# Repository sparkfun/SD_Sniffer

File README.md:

SD Sniffer
==========

[
*SD Sniffer (TOL-11468)*](https://www.sparkfun.com/products/11468)

The SD Sniffer allows you to hook up an external device to view SPI signals between an SD socket and SD card.

Repository Contents
-------------------
* **/Hardware** - All Eagle design files (.brd, .sch, .STL)
* **/Production** - Test bed files and production panel files

License Information
-------------------
The hardware is released under [Creative Commons ShareAlike 4.0 International](https://creativecommons.org/licenses/by-sa/4.0/).

Distributed as-is; no warranty is given.

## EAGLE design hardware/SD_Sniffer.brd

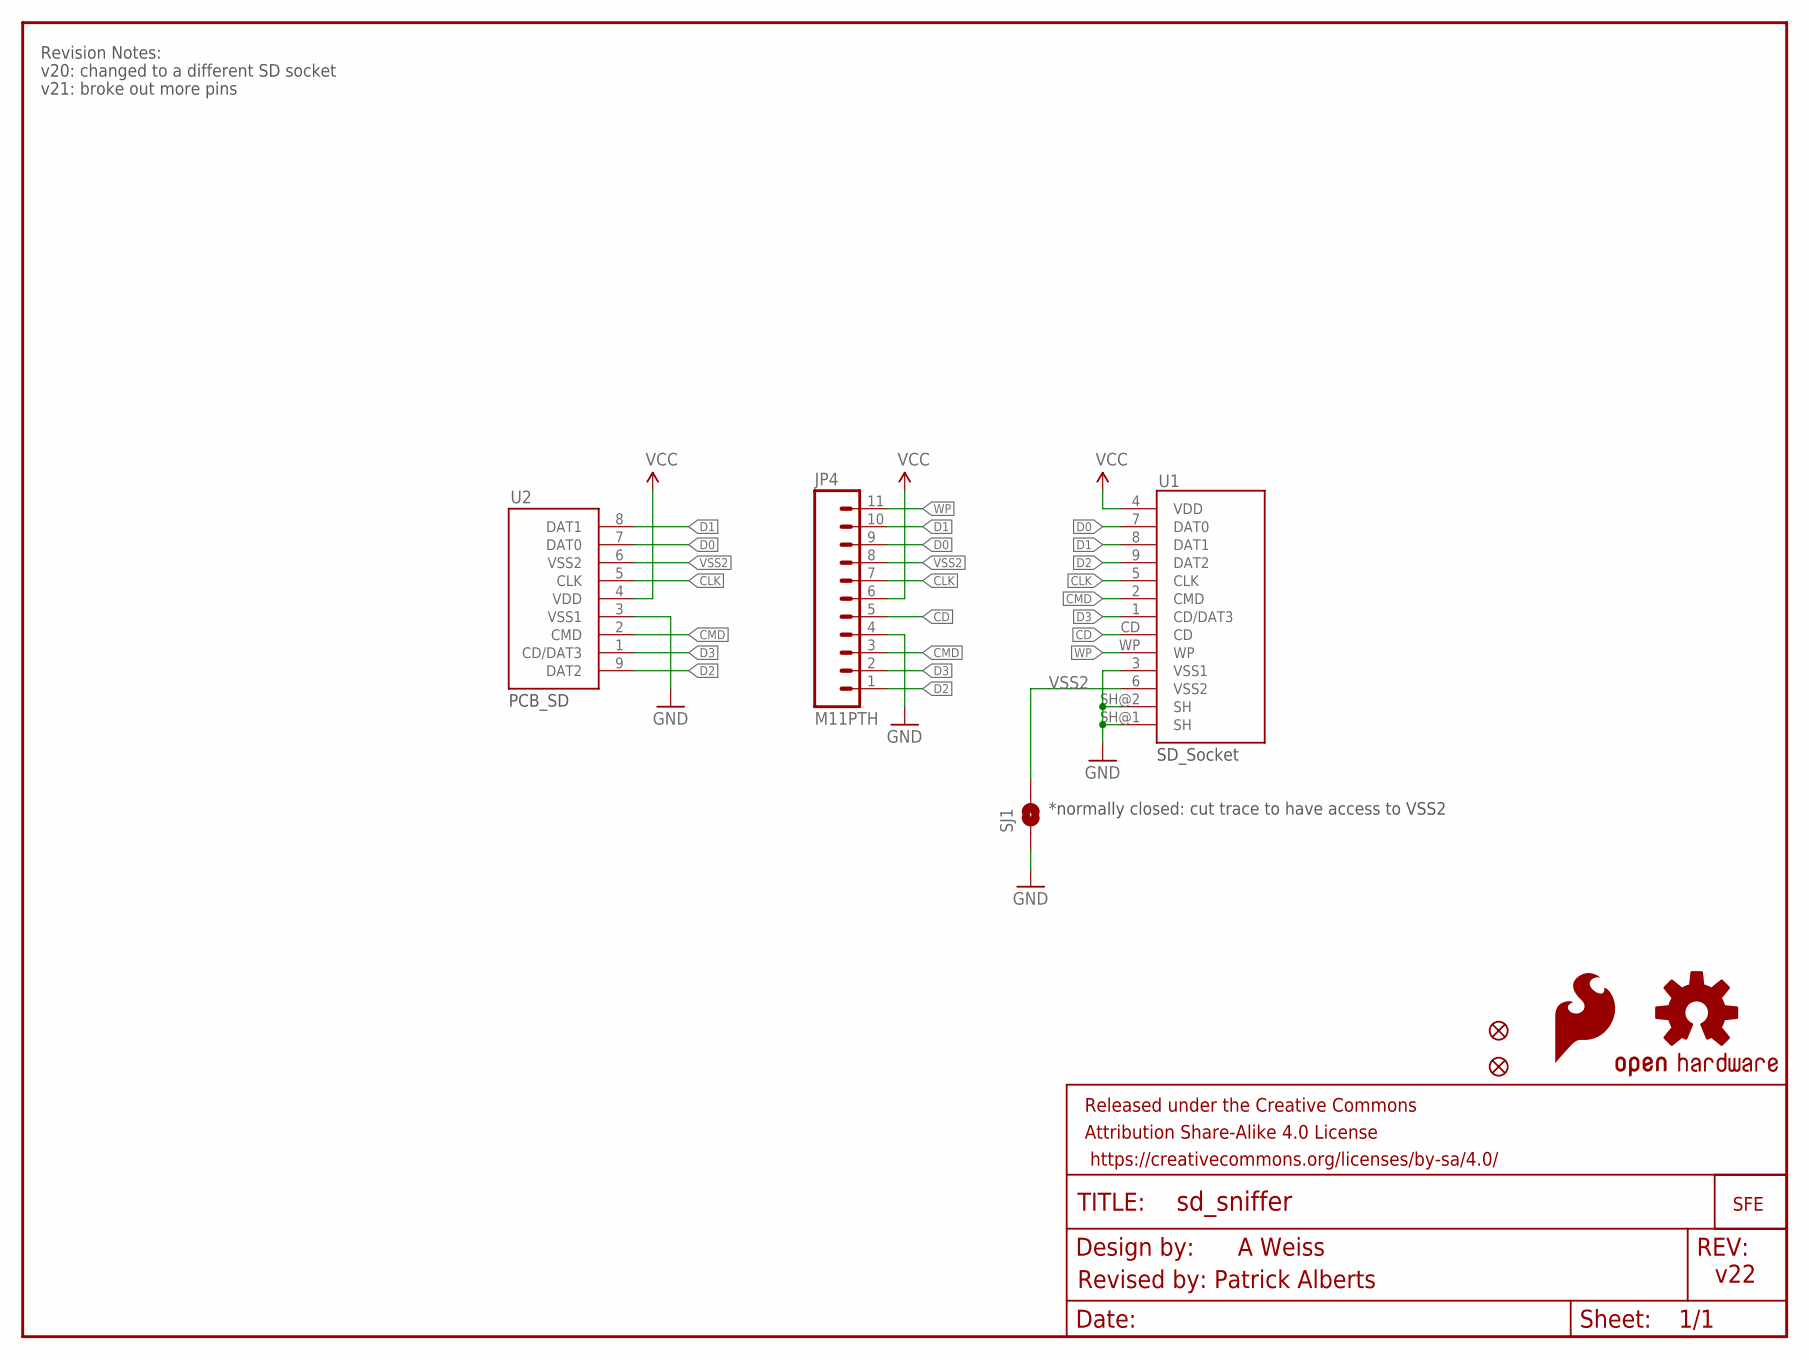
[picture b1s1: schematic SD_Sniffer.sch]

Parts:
FRAME1: FRAME-LETTER; CREATIVE_COMMONS
JP2, JP3: FIDUCIALUFIDUCIAL; MICRO-FIDUCIAL
JP4: M11PTH; 1X11
LOGO: LOGO-SFENEW; SFE-NEW-WEBLOGO
SJ1: SOLDERJUMPERTRACE; SJ_2S-TRACE
U1: SD_CARD_SOCKET; SD_1:1
U2: SD_MMC_CARDSD_PCB; SD-MMC-CARD
U$2: OSHW-LOGOS; OSHW-LOGO-S
U$4: SFE_LOGO_FLAME.2_INCH; SFE_LOGO_FLAME_.2

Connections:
CD: JP4.5, U1.CD
CLK: JP4.7, U1.5 (CLK), U2.5 (CLK)
CMD: JP4.3, U1.2 (CMD), U2.2 (CMD)
D0: JP4.9, U1.7 (DAT0), U2.7 (DAT0)
D1: JP4.10, U1.8 (DAT1), U2.8 (DAT1)
D2: JP4.1, U1.9 (DAT2), U2.9 (DAT2)
D3: JP4.2, U1.1 (CD/DAT3), U2.1 (CD/DAT3)
GND: JP4.4, SJ1.1, U1.3 (VSS1), U1.SH@1 (SH), U1.SH@2 (SH), U2.3 (VSS1)
VCC: JP4.6, U1.4 (VDD), U2.4 (VDD)
VSS2: JP4.8, SJ1.2, U1.6 (VSS2), U2.6 (VSS2)
WP: JP4.11, U1.WP

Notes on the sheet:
PCB_SD
SD_Socket
Revision Notes:
v20: changed to a different SD socket
*normally closed: cut trace to have access to VSS2
v21: broke out more pins
v22
A Weiss
Revised by: Patrick Alberts

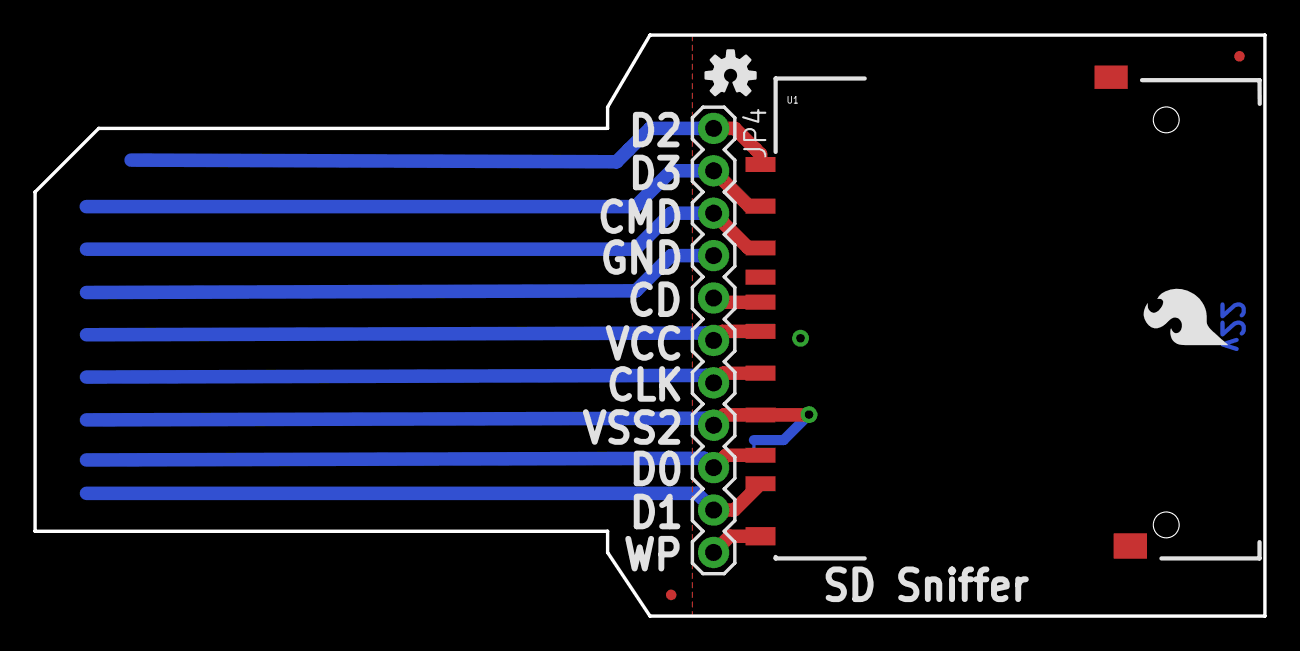
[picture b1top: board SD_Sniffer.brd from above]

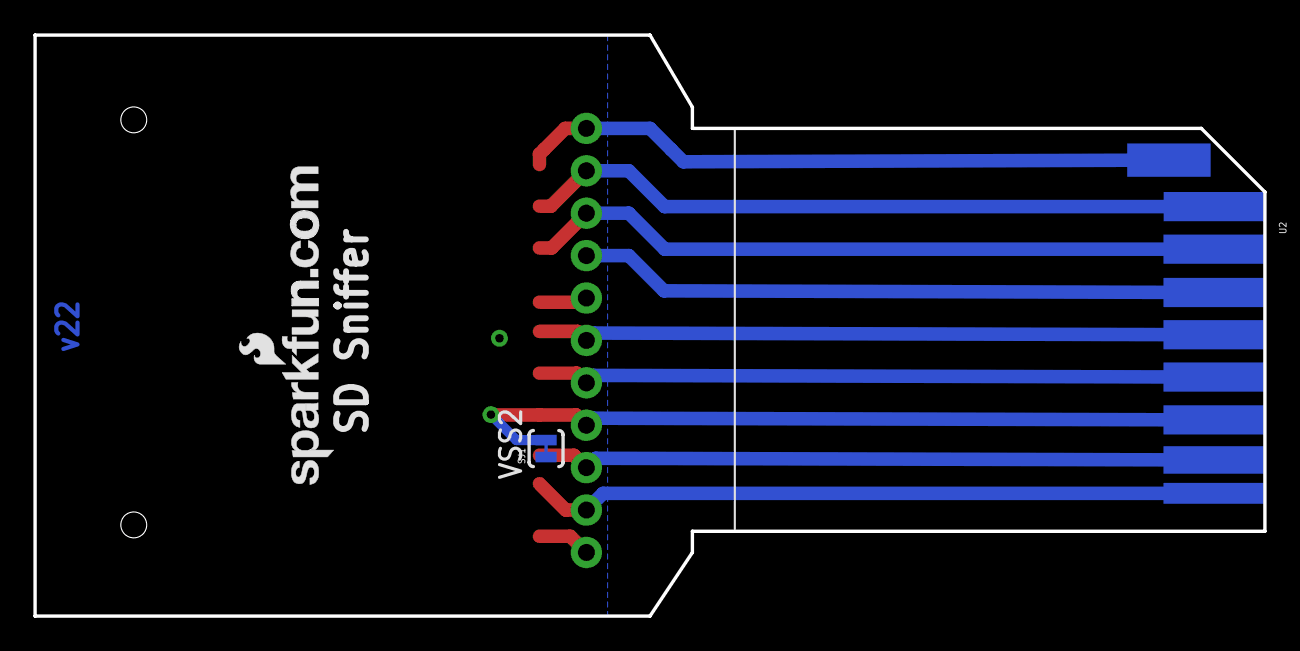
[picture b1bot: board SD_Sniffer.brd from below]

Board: 2 copper layers, 73.7 x 34.8 mm, 10 parts (3 on the bottom side), 11 nets.

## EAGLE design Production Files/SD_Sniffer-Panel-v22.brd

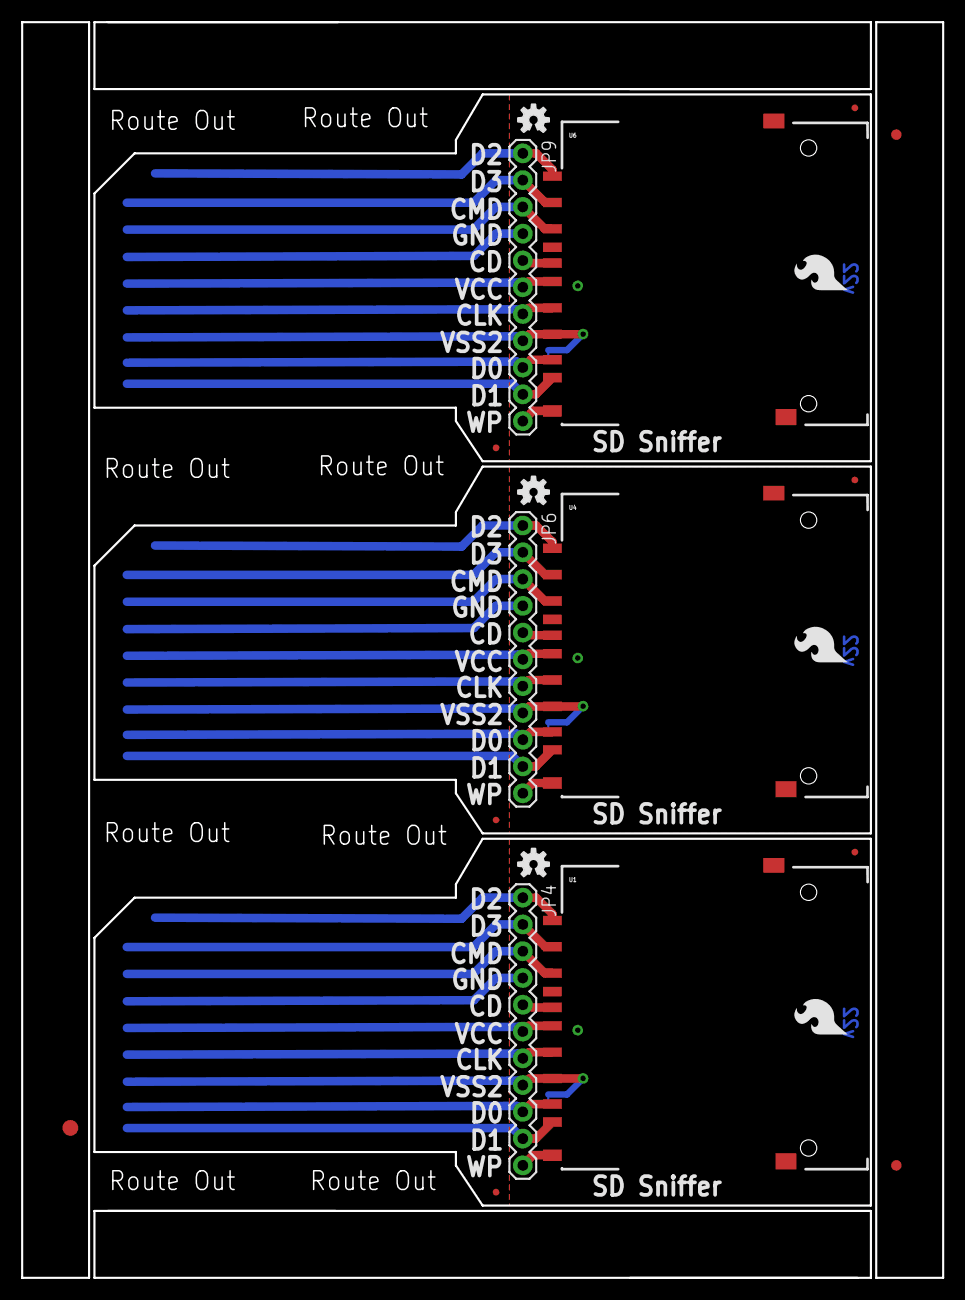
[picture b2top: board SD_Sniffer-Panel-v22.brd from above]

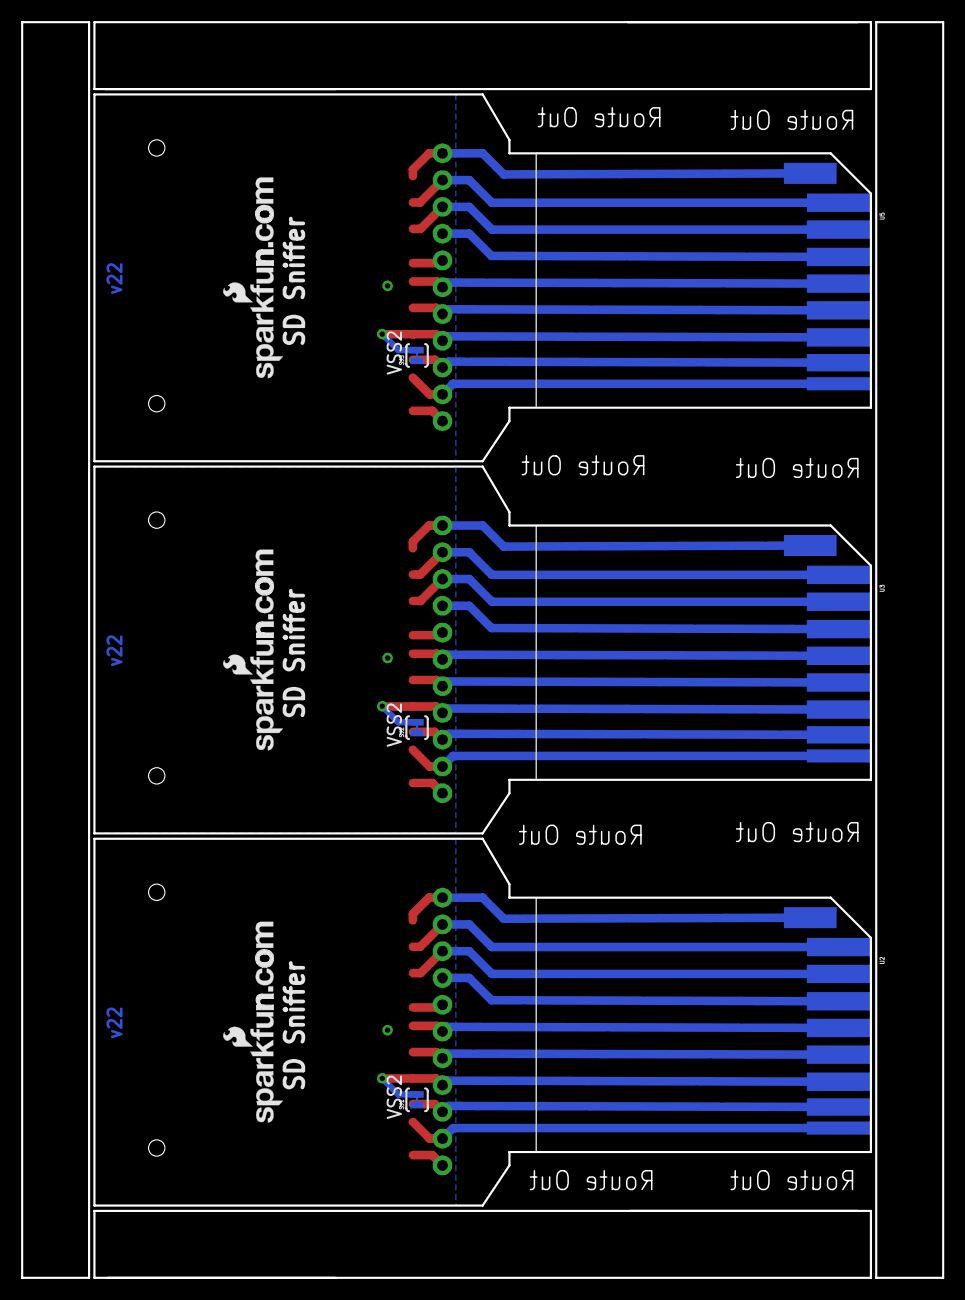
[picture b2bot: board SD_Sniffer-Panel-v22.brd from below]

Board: 2 copper layers, 87.4 x 119.1 mm, 30 parts (9 on the bottom side), 33 nets.

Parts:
E$1: FIDUCIAL-1.5X3
E$2, E$3: FIDUCIAL-1X2
JP1, JP2, JP3, JP5, JP7, JP8: FIDUCIALUFIDUCIAL; MICRO-FIDUCIAL
JP4, JP6, JP9: M11PTH; 1X11
LOGO, LOGO1, LOGO2: LOGO-SFENEW; SFE-NEW-WEBLOGO
SJ1, SJ2, SJ3: SOLDERJUMPERTRACE; SJ_2S-TRACE
U1, U4, U6: SD_CARD_SOCKET; SD_1:1
U2, U3, U5: SD_MMC_CARDSD_PCB; SD-MMC-CARD
U$1, U$4, U$5: SFE_LOGO_FLAME.2_INCH; SFE_LOGO_FLAME_.2
U$2, U$3, U$6: OSHW-LOGOS; OSHW-LOGO-S

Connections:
CD: JP4.5, U1.CD
CD1: JP6.5, U4.CD
CD2: JP9.5, U6.CD
CLK: JP4.7, U1.5, U2.5
CLK1: JP6.7, U3.5, U4.5
CLK2: JP9.7, U5.5, U6.5
CMD: JP4.3, U1.2, U2.2
CMD1: JP6.3, U3.2, U4.2
CMD2: JP9.3, U5.2, U6.2
D0: JP4.9, U1.7, U2.7
D1: JP4.10, U1.8, U2.8
D2: JP4.1, U1.9, U2.9
D3: JP4.2, U1.1, U2.1
D4: JP6.1, U3.9, U4.9
D5: JP6.9, U3.7, U4.7
D6: JP6.10, U3.8, U4.8
D7: JP6.2, U3.1, U4.1
D8: JP9.1, U5.9, U6.9
D9: JP9.9, U5.7, U6.7
D10: JP9.10, U5.8, U6.8
D11: JP9.2, U5.1, U6.1
GND: JP4.4, SJ1.1, U1.3, U1.SH@1, U1.SH@2, U2.3
GND1: JP6.4, SJ2.1, U3.3, U4.3, U4.SH@1, U4.SH@2
GND2: JP9.4, SJ3.1, U5.3, U6.3, U6.SH@1, U6.SH@2
VCC: JP4.6, U1.4, U2.4
VCC1: JP6.6, U3.4, U4.4
VCC2: JP9.6, U5.4, U6.4
VSS1: JP6.8, SJ2.2, U3.6, U4.6
VSS2: JP4.8, SJ1.2, U1.6, U2.6
VSS3: JP9.8, SJ3.2, U5.6, U6.6
WP: JP4.11, U1.WP
WP1: JP6.11, U4.WP
WP2: JP9.11, U6.WP

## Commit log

2014-04-23 Initial Commit with BRD/SCH
2014-05-02 Moved via, Added Bigger Flame, Named Jumper
2014-05-02 Added updated SD socket
2014-05-27 Fixed eagle sync
2014-05-27 created panel v22
2014-07-03 Cleaning up README, adding git files

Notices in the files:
parts and their libraries:
SparkFun-Connectors: Licensing: CC v3.0 Share-Alike You are welcome to use this library for commercial purposes.
SparkFun-Boards: Licensing: Creative Commons ShareAlike 4.0 International - https://creativecommons.org/licenses/by-sa/4.0
SparkFun-Aesthetics: Released under the Creative Commons
